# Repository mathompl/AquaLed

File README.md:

# AquaLed (en)

Arduino PWM LED lamp driver software with LCD support and temperature control for marine, reef or sweetwater aquariums.

Features:
- 8 channel PWM control of LED modules (drivers), with I2C module up to 512 (up to 8 channels on LCD)
- programmable light hours with sunsets and sunrises
- night light support
- 3 digital thermometers with asynchronous temperature read, for: water, lamp and addictional lamp or sump, controlling 3 separate  relays (cooling fans)
- customizable dimming, linear or logarithmic algorith
- bluetooth compatibility with AQma Led Control by Maqu http://magu.pl/aqma-led-control
- full configuration and status using Nextion 2.8" LCD with touch support, including: operational hours, sunset & sunrise hours, thermometers, dimming times, schedule, night mode etc.
- override programs: off, night and user accessible from LCD
- date/time support with RTC module
- screen saver with water temperature and time
- test mode
- moonphases simulation for night light
- all settings stored in EEPROM
- works on Arduino Nano

Example Nextion project attached. I dont have copyright for graphics used, use only as an example.

**Nextion LCD Screenshots**

**REQUIREMENTS:**

**Hardware:**
- Arduino Nano or better
- RTC module 
- Bluetooth (optional)
- 3x DS18B20 digital thermometers
- 3x 5v relays modules
- PCA9685 PWM i2c module (optional)
- Nextion 2.8" LCD

**Libraries:**
- Arduino-Temperature-Control-Library (https://github.com/milesburton/Arduino-Temperature-Control-Library) 
- DS1307RTC (https://github.com/PaulStoffregen/DS1307RTC)
- DS18B20 (https://github.com/nettigo/DS18B20)
- OneWire (https://github.com/PaulStoffregen/OneWire)
- Time (https://github.com/PaulStoffregen/Time)
- Adafruit-PWM-Servo-Driver-Library (https://github.com/adafruit/Adafruit-PWM-Servo-Driver-Library)
- or https://github.com/NachtRaveVL/PCA9685-Arduino

**Software:**
- Nextion Editor (https://nextion.itead.cc/download.html)
- Arduino IDE or atom.io

**Configuration:**
Driver configuration is in file aqualed.h

####PINS SETUP:
Configuration on LCD.

####Modules (uncomment to disable). As for now bluetooth and nextion support does not fit into Arduino Nano/UNO etc. flash memory. Use arduino Mega or disable one module support.
```
// modules, uncomment to disable, comment to enable
#define NO_BLUETOOTH
//#define NO_NEXTION
//#define NO_TEMPERATURE
```
####Other
There are many other options for eg. timers resolution, most of them are pretty self-explanatory ;)

**Wiring:**

# AquaLed (pl)

Sterownik lampy LED PWM na Arduino z obsługą termometrów, chłodzenia i wyświetlacza LCD Nextion dla akwariów słodko i słonowodnych.

Możliwości:
- obsługa 8 ściemnialnych kanałów PWM dla modułów LED (driverów), z modułem I2C do 512 kanałów (maksymalnie 8 na wyswietlaczu)
- programowanie godzin świetenia z symulacją wschodów i zachodów słońca
- światło nocne
- obsługa 3 cyfrowych termometrów sterujących pracą 3 przekaźników (np. wentylatorów), np. dla lampy, lampy w sumpie, wody w akwarium
- ściemnianie/rozjaśnianie
- kompatybilność z AQma Led Control by Maqu http://magu.pl/aqma-led-control w zakresie programowania przez Bluetooth
- pełna konfiguracja i status za pomocą wyświetlacza Nextion LCD (przykłady na 2,8"), sterowanie przez dotyk.
- możliwość chwilowego nadpisania działającego programu z wyświetlacza: wyłączenie/wymuszenie światła nocnego/program zdefiniowany
- obsługa godziny i daty
- wygaszacz ekranu z godziną i temperaturą wody
- tryb test
- symulacja faz księżyca
- wszystkie ustawienia zapamiętywane w pamięci EEPROM
- działa z Arduino Nano lub wyższym modelem

Przykładowy program na wyświetlacz załączony.

**Wygląd ekranów na wyświetlaczu **

**Wymagania:**

**Sprzęt:**
- Arduino Nano lub wyższy
- moduł czasu rzeczywistego RTC
- Bluetooth (opcjonalnie)
- 3x termometry cyfrowe DS18B20
- 3x moduły przekaźników 5v
- moduł PCA9685 PWM i2c  (optionalny)
- wyświetlacz Nextion 2.8" LCD lub większy

**Biblioteki:**
- Arduino-Temperature-Control-Library (https://github.com/milesburton/Arduino-Temperature-Control-Library)
- DS1307RTC (https://github.com/PaulStoffregen/DS1307RTC)
- DS18B20 (https://github.com/nettigo/DS18B20)
- OneWire (https://github.com/PaulStoffregen/OneWire)
- Time (https://github.com/PaulStoffregen/Time)
- Adafruit-PWM-Servo-Driver-Library (https://github.com/adafruit/Adafruit-PWM-Servo-Driver-Library)
- lub https://github.com/NachtRaveVL/PCA9685-Arduino

**Oprogramowanie:**
- Nextion Editor (https://nextion.itead.cc/download.html)
- Arduino IDE lub atom.io

**Konfiguracja:**
Konfiguracja w pliku aqualed.h i nextion.h

####Ustawienia pinów PWM:
Konfiguracja z poziomu wyświetlacza.

####Moduły (odkomentuj żeby wyłączyć). Uwaga! Obsługa bluetooth i nextio nie mieści się jednocześnie w pamięcy flash Arduino Nano/Uno itd. wchodzi tylko do Arduino Mega lub podobnego.
```
// modules, uncomment to disable, comment to enable
#define NO_BLUETOOTH
//#define NO_NEXTION
//#define NO_TEMPERATURE
```
####Inne
W pliku konfiguracyjnym można ustawić wiele opcji w tym czasy działania timerów, rozdzielczość załączania przekaźników itd. Większość ustawień wynika z samych nazw stałych :)

**Podłączenie:**

**PCB Prototype boards:**

Support:http://nano-reef.pl/topic/88904-a-qualed-sterownik-led-termometry-lcd-nextion/

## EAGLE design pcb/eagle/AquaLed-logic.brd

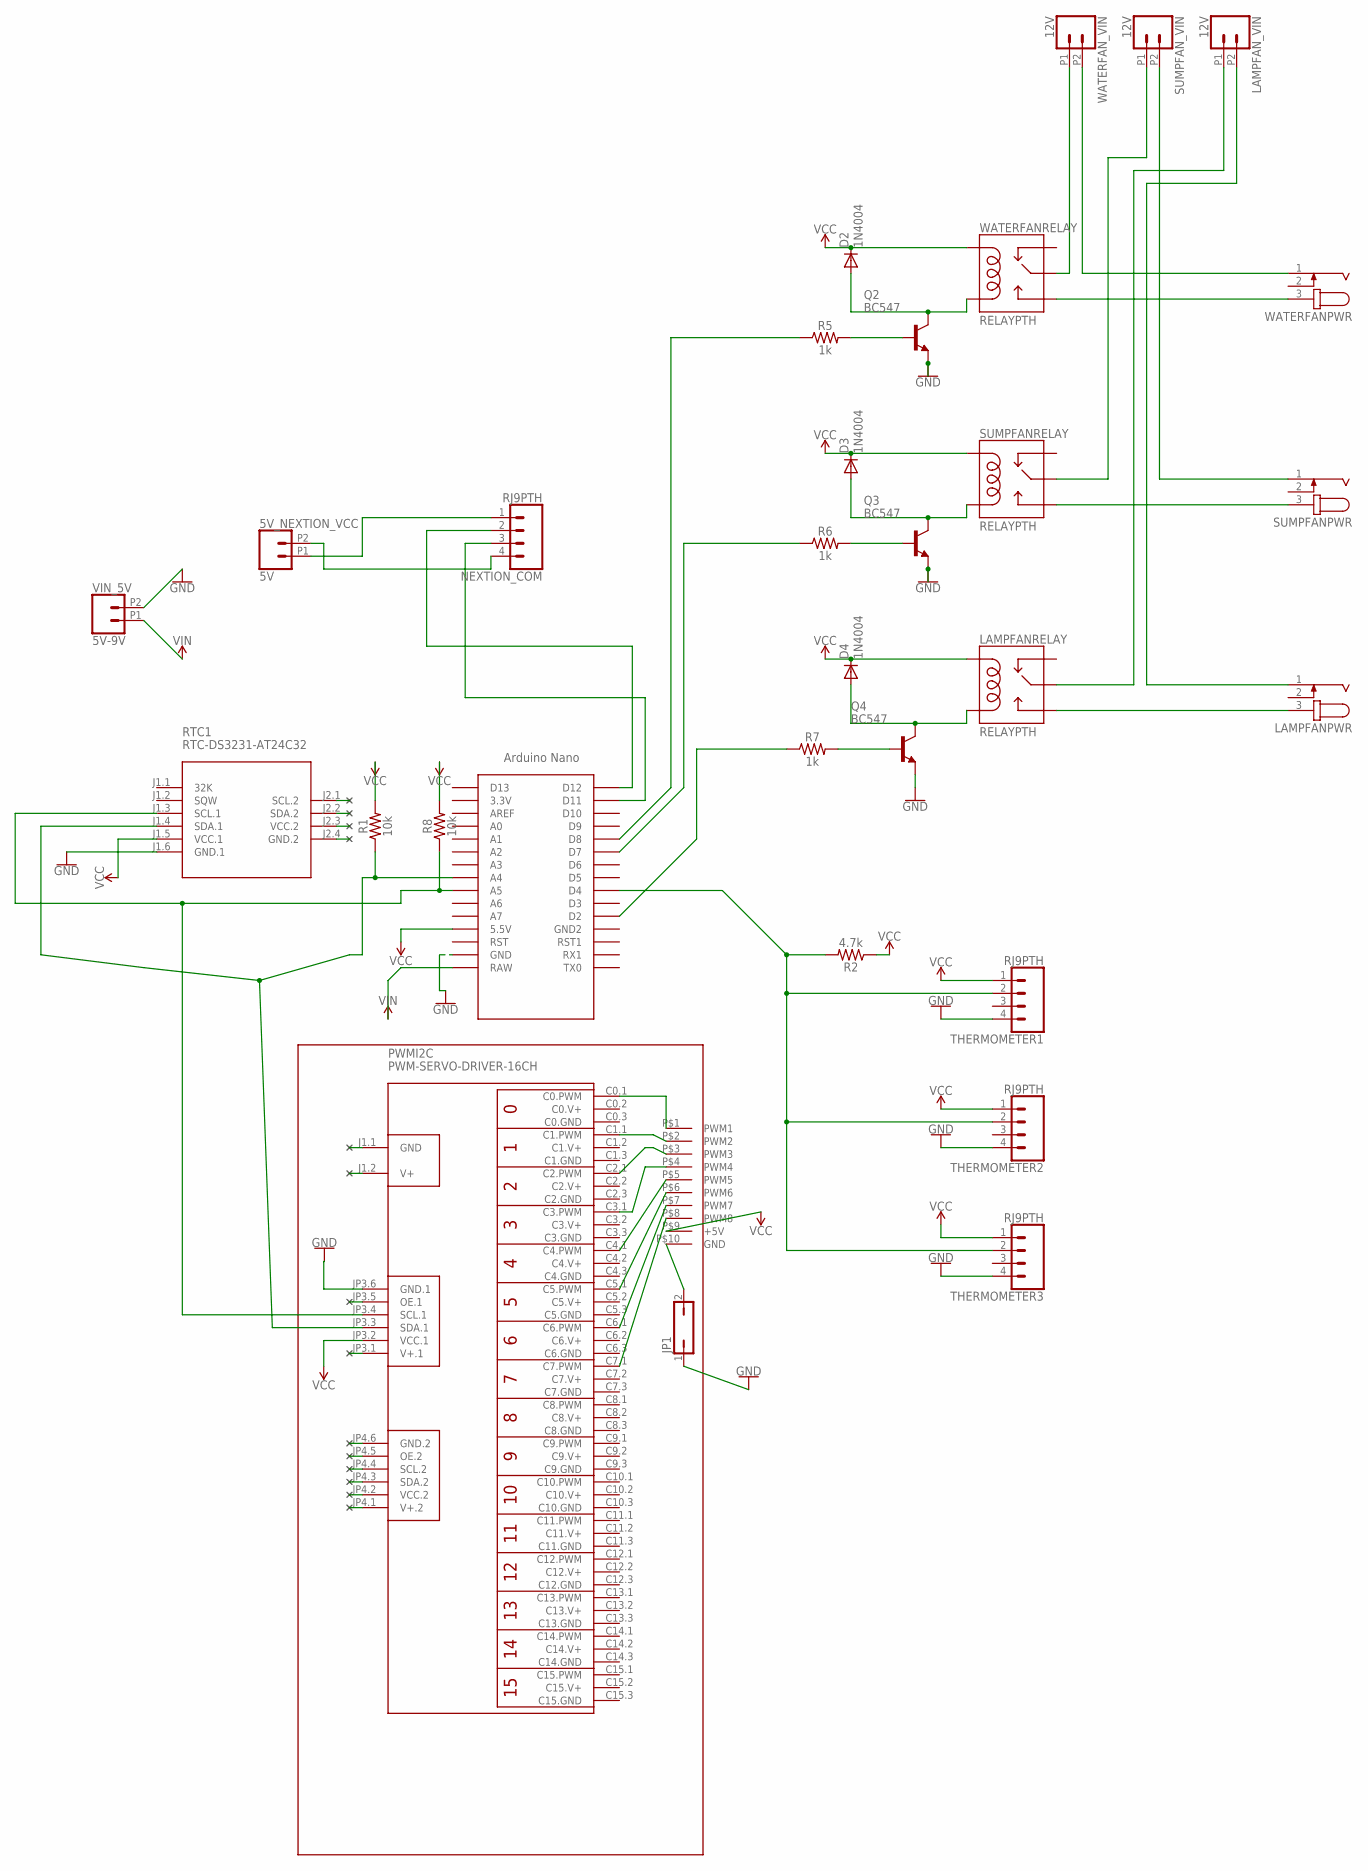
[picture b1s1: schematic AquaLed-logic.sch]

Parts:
5V_NEXTION_VCC: 5V; 1X02_2.54_SCREWTERM
D2, D3, D4: 1N4004; DO41-10
JP1: JP1Q; JP1
LAMPFANPWR: JACK-PLUG1; SPC4078
LAMPFANRELAY: RELAYPTH; SRD-05VDC-SL-C
LAMPFAN_VIN: 12V; 1X02_2.54_SCREWTERM
NEXTION_COM: RJ9PTH; RJ9
PWMI2C: PWM-SERVO-DRIVER-16CH
Q2, Q3, Q4: BC547; TO92
R1, R8: 10k; AXIAL-0.3
R2: 4.7k; AXIAL-0.3
R5, R6, R7: 1k; AXIAL-0.3
RTC1: RTC-DS3231-AT24C32
SUMPFANPWR: JACK-PLUG1; SPC4078
SUMPFANRELAY: RELAYPTH; SRD-05VDC-SL-C
SUMPFAN_VIN: 12V; 1X02_2.54_SCREWTERM
THERMOMETER1, THERMOMETER2, THERMOMETER3: RJ9PTH; RJ9
U$1: NANO
U$29: PCB
VIN_5V: 5V-9V; 1X02_2.54_SCREWTERM
WATERFANPWR: JACK-PLUG1; SPC4078
WATERFANRELAY: RELAYPTH; SRD-05VDC-SL-C
WATERFAN_VIN: 12V; 1X02_2.54_SCREWTERM

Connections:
GND: JP1.1, PWMI2C.JP3.6 (GND.1), Q2.1 (E), Q3.1 (E), Q4.1 (E), RTC1.J1.6 (GND.1), THERMOMETER1.4, THERMOMETER2.4, THERMOMETER3.4, U$1.GND, VIN_5V.P2 (2)
unnamed: R2.P$2 (2), THERMOMETER1.2, THERMOMETER2.2, THERMOMETER3.2, U$1.D4
unnamed: PWMI2C.JP3.3 (SDA.1), R1.P$1 (1), RTC1.J1.4 (SDA.1), U$1.A4
unnamed: R5.P$1 (1), U$1.D8
unnamed: R6.P$1 (1), U$1.D7
unnamed: LAMPFANPWR.3, LAMPFANRELAY.SWOPEN
unnamed: SUMPFANPWR.3, SUMPFANRELAY.SWOPEN
unnamed: LAMPFANRELAY.SWCOMMON, LAMPFAN_VIN.P1 (1)
unnamed: R7.P$1 (1), U$1.D2
unnamed: D2.A, Q2.3 (C), WATERFANRELAY.COIL0
unnamed: Q2.2 (B), R5.P$2 (2)
unnamed: SUMPFANPWR.1, SUMPFAN_VIN.P2 (2)
unnamed: D3.A, Q3.3 (C), SUMPFANRELAY.COIL0
unnamed: Q3.2 (B), R6.P$2 (2)
unnamed: LAMPFANPWR.1, LAMPFAN_VIN.P2 (2)
unnamed: D4.A, LAMPFANRELAY.COIL0, Q4.3 (C)
unnamed: Q4.2 (B), R7.P$2 (2)
unnamed: SUMPFANRELAY.SWCOMMON, SUMPFAN_VIN.P1 (1)
unnamed: WATERFANRELAY.SWCOMMON, WATERFAN_VIN.P1 (1)
unnamed: WATERFANPWR.1, WATERFAN_VIN.P2 (2)
unnamed: WATERFANPWR.3, WATERFANRELAY.SWOPEN
unnamed: 5V_NEXTION_VCC.P1 (1), NEXTION_COM.1
unnamed: 5V_NEXTION_VCC.P2 (2), NEXTION_COM.4
unnamed: NEXTION_COM.3, U$1.D11
unnamed: NEXTION_COM.2, U$1.D12
unnamed: PWMI2C.JP3.4 (SCL.1), R8.P$1 (1), RTC1.J1.3 (SCL.1), U$1.A5
unnamed: PWMI2C.C0.1 (C0.PWM), U$29.P$1 (PWM1)
unnamed: PWMI2C.C1.1 (C1.PWM), U$29.P$2 (PWM2)
unnamed: PWMI2C.C2.1 (C2.PWM), U$29.P$3 (PWM3)
unnamed: PWMI2C.C3.1 (C3.PWM), U$29.P$4 (PWM4)
unnamed: PWMI2C.C4.1 (C4.PWM), U$29.P$5 (PWM5)
unnamed: PWMI2C.C5.1 (C5.PWM), U$29.P$6 (PWM6)
unnamed: PWMI2C.C6.1 (C6.PWM), U$29.P$7 (PWM7)
unnamed: PWMI2C.C7.1 (C7.PWM), U$29.P$8 (PWM8)
unnamed: JP1.2, U$29.P$10 (GND)
VCC: D2.C, D3.C, D4.C, LAMPFANRELAY.COIL1, PWMI2C.JP3.2 (VCC.1), R1.P$2 (2), R2.P$1 (1), R8.P$2 (2), RTC1.J1.5 (VCC.1), SUMPFANRELAY.COIL1, THERMOMETER1.1, THERMOMETER2.1, THERMOMETER3.1, U$1.5V (5.5V), U$29.P$9 (+5V), WATERFANRELAY.COIL1
VIN: U$1.RAW, VIN_5V.P1 (1)

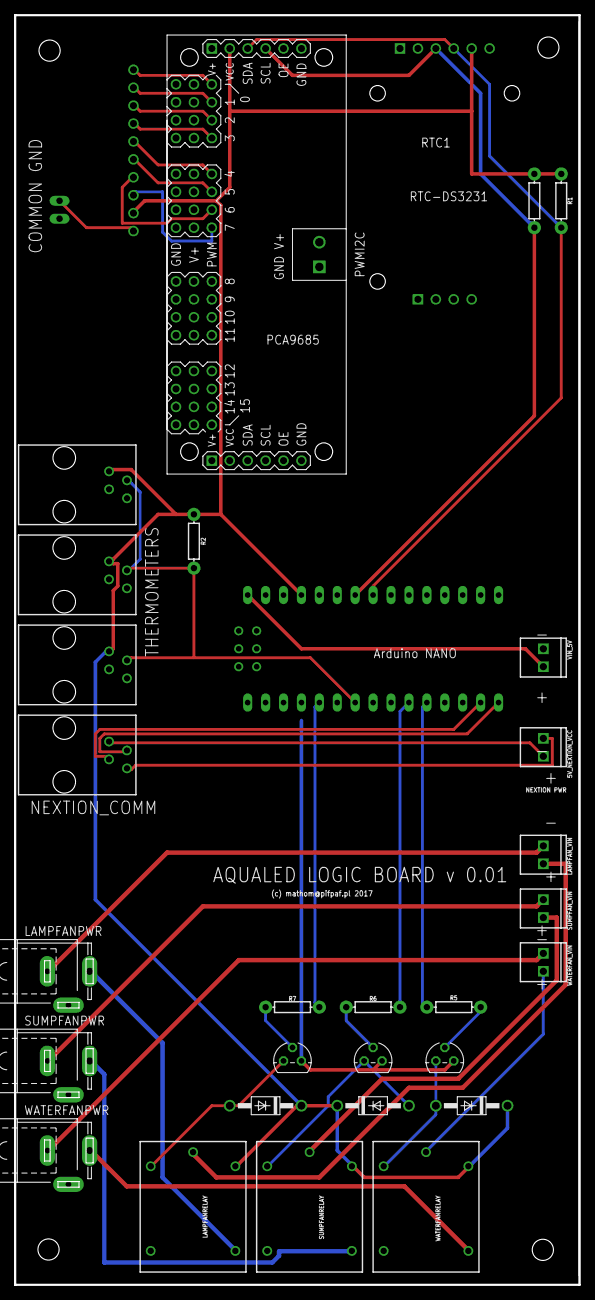
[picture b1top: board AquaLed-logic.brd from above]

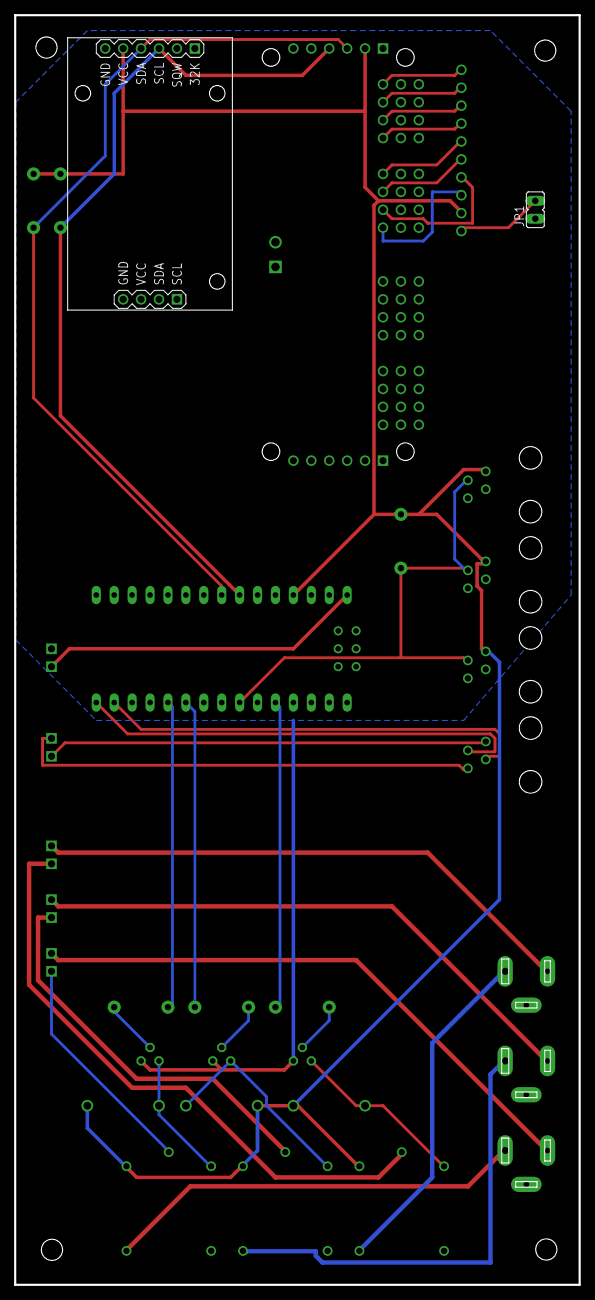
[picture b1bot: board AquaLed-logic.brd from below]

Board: 2 copper layers, 80.0 x 180.0 mm, 32 parts (2 on the bottom side), 37 nets.

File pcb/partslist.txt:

Partlist

Exported from AquaLEd-drivers.sch at 2017-11-26 09:05

EAGLE Version 8.4.1 Copyright (c) 1988-2017 Autodesk, Inc.

Assembly variant:

Part     Value          Device     Package  Library          Sheet

DRIVER1                 LDD-H      LDD-H    meanwell_dcdc_v8 1
DRIVER2                 LDD-H      LDD-H    meanwell_dcdc_v8 1
DRIVER3                 LDD-H      LDD-H    meanwell_dcdc_v8 1
DRIVER4                 LDD-H      LDD-H    meanwell_dcdc_v8 1
DRIVER5                 LDD-H      LDD-H    meanwell_dcdc_v8 1
DRIVER6                 LDD-H      LDD-H    meanwell_dcdc_v8 1
DRIVER7                 LDD-H      LDD-H    meanwell_dcdc_v8 1
DRIVER8                 LDD-H      LDD-H    meanwell_dcdc_v8 1
POWERIN                 W237-102   W237-102 con-wago-500     1
PWM1                    JACK-PLUG1 SPC4078  con-jack         1
PWM2                    JACK-PLUG1 SPC4078  con-jack         1
PWM3                    JACK-PLUG1 SPC4078  con-jack         1
PWM4                    JACK-PLUG1 SPC4078  con-jack         1
PWM5                    JACK-PLUG1 SPC4078  con-jack         1
PWM6                    JACK-PLUG1 SPC4078  con-jack         1
PWM7                    JACK-PLUG1 SPC4078  con-jack         1
PWM8                    JACK-PLUG1 SPC4078  con-jack         1

Partlist

Exported from AquaLed-logic.sch at 2017-11-26 09:06

EAGLE Version 8.4.1 Copyright (c) 1988-2017 Autodesk, Inc.

Assembly variant:

Part           Value                 Device                  Package               Library             Sheet

5V_NEXTION_VCC 5V                    CONN_022.54MM_SCREWTERM 1X02_2.54_SCREWTERM   SparkFun-Connectors 1
D2             1N4004                1N4004                  DO41-10               diode               1
D3             1N4004                1N4004                  DO41-10               diode               1
D4             1N4004                1N4004                  DO41-10               diode               1
JP1                                  JP1Q                    JP1                   jumper              1
LAMPFANPWR                           JACK-PLUG1              SPC4078               con-jack            1
LAMPFANRELAY   RELAYPTH              RELAYPTH                SRD-05VDC-SL-C        SRD-05VDC-SL-C      1
LAMPFAN_VIN    12V                   CONN_022.54MM_SCREWTERM 1X02_2.54_SCREWTERM   SparkFun-Connectors 1
NEXTION_COM    RJ9PTH                RJ9PTH                  RJ9                   SparkFun-Retired    1
PWMI2C         PWM-SERVO-DRIVER-16CH PWM-SERVO-DRIVER-16CH   PWM-SERVO-DRIVER-16CH diy-modules         1
Q2             BC547                 BC547                   TO92                  transistor-npn      1
Q3             BC547                 BC547                   TO92                  transistor-npn      1
Q4             BC547                 BC547                   TO92                  transistor-npn      1
R1             10k                   10KOHM-HORIZ-1/6W-5%    AXIAL-0.3             SparkFun-Resistors  1
R2             4.7k                  RESISTORAXIAL-0.3       AXIAL-0.3             SparkFun-Resistors  1
R5             1k                    10KOHM-HORIZ-1/4W-1%    AXIAL-0.3             SparkFun-Resistors  1
R6             1k                    10KOHM-HORIZ-1/4W-1%    AXIAL-0.3             SparkFun-Resistors  1
R7             1k                    10KOHM-HORIZ-1/4W-1%    AXIAL-0.3             SparkFun-Resistors  1
R8             10k                   10KOHM-HORIZ-1/6W-5%    AXIAL-0.3             SparkFun-Resistors  1
RTC1           RTC-DS3231-AT24C32    RTC-DS3231-AT24C32      RTC-DS3231-AT24C32    diy-modules         1
SUMPFANPWR                           JACK-PLUG1              SPC4078               con-jack            1
SUMPFANRELAY   RELAYPTH              RELAYPTH                SRD-05VDC-SL-C        SRD-05VDC-SL-C      1
SUMPFAN_VIN    12V                   CONN_022.54MM_SCREWTERM 1X02_2.54_SCREWTERM   SparkFun-Connectors 1
THERMOMETER1   RJ9PTH                RJ9PTH                  RJ9                   SparkFun-Retired    1
THERMOMETER2   RJ9PTH                RJ9PTH                  RJ9                   SparkFun-Retired    1
THERMOMETER3   RJ9PTH                RJ9PTH                  RJ9                   SparkFun-Retired    1
U$1            NANO                  NANO                    NANO                  Arduino-clone       1
U$29           PCB                   PCB                     PCB                   aqualed             1
VIN_5V         5V-9V                 CONN_022.54MM_SCREWTERM 1X02_2.54_SCREWTERM   SparkFun-Connectors 1
WATERFANPWR                          JACK-PLUG1              SPC4078               con-jack            1
WATERFANRELAY  RELAYPTH              RELAYPTH                SRD-05VDC-SL-C        SRD-05VDC-SL-C      1
WATERFAN_VIN   12V                   CONN_022.54MM_SCREWTERM 1X02_2.54_SCREWTERM   SparkFun-Connectors 1

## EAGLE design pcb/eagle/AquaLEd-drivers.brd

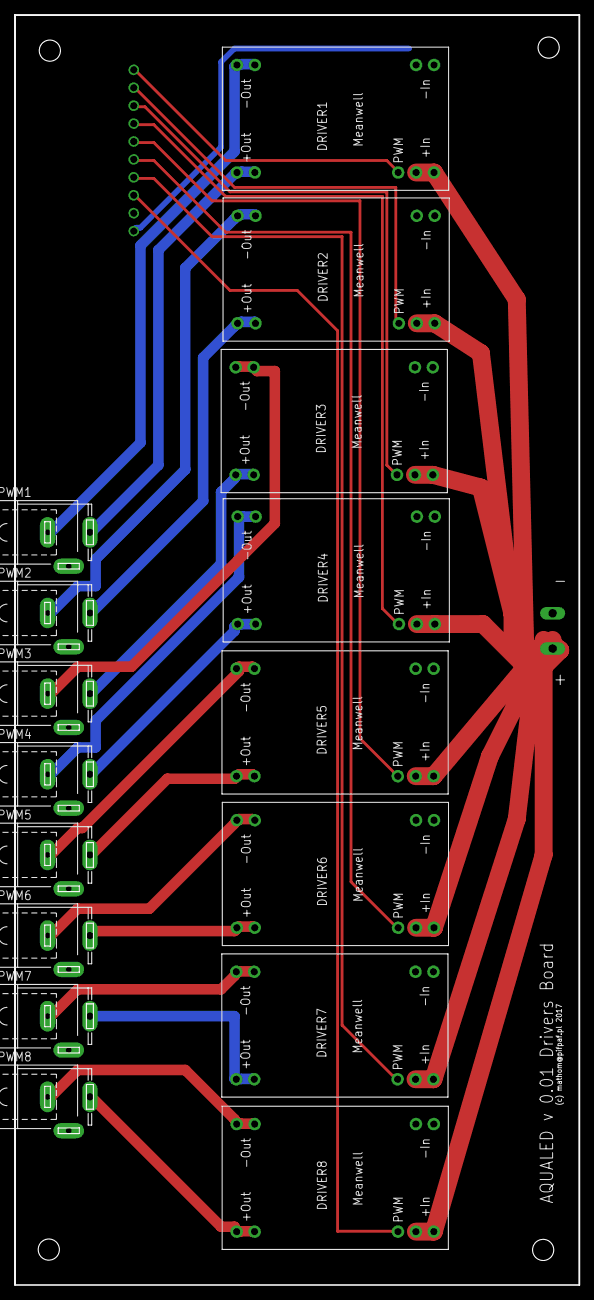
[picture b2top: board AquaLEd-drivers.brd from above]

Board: 2 copper layers, 80.0 x 180.0 mm, 18 parts (1 on the bottom side), 26 nets.

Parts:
DRIVER1, DRIVER2, DRIVER3, DRIVER4, DRIVER5, DRIVER6, DRIVER7, DRIVER8: LDD-H
POWERIN: W237-102
PWM1, PWM2, PWM3, PWM4, PWM5, PWM6, PWM7, PWM8: SPC4078
U$29: PCB

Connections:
GND: DRIVER1.1, DRIVER1.2, DRIVER2.1, DRIVER2.2, DRIVER3.1, DRIVER3.2, DRIVER4.1, DRIVER4.2, DRIVER5.1, DRIVER5.2, DRIVER6.1, DRIVER6.2, DRIVER7.1, DRIVER7.2, DRIVER8.1, DRIVER8.2, POWERIN.1, U$29.P$10
unnamed: DRIVER1.22, U$29.P$1
unnamed: DRIVER8.11, DRIVER8.12, PWM8.1
unnamed: DRIVER8.13, DRIVER8.14, PWM8.3
unnamed: DRIVER7.11, DRIVER7.12, PWM7.1
unnamed: DRIVER7.13, DRIVER7.14, PWM7.3
unnamed: DRIVER6.11, DRIVER6.12, PWM6.1
unnamed: DRIVER6.13, DRIVER6.14, PWM6.3
unnamed: DRIVER5.11, DRIVER5.12, PWM5.1
unnamed: DRIVER5.13, DRIVER5.14, PWM5.3
unnamed: DRIVER4.11, DRIVER4.12, PWM4.1
unnamed: DRIVER4.13, DRIVER4.14, PWM4.3
unnamed: DRIVER3.11, DRIVER3.12, PWM3.1
unnamed: DRIVER3.13, DRIVER3.14, PWM3.3
unnamed: DRIVER2.11, DRIVER2.12, PWM2.1
unnamed: DRIVER2.13, DRIVER2.14, PWM2.3
unnamed: DRIVER1.11, DRIVER1.12, PWM1.1
unnamed: DRIVER1.13, DRIVER1.14, PWM1.3
unnamed: DRIVER2.22, U$29.P$2
unnamed: DRIVER3.22, U$29.P$3
unnamed: DRIVER4.22, U$29.P$4
unnamed: DRIVER5.22, U$29.P$5
unnamed: DRIVER6.22, U$29.P$6
unnamed: DRIVER7.22, U$29.P$7
unnamed: DRIVER8.22, U$29.P$8
VIN: DRIVER1.23, DRIVER1.24, DRIVER2.23, DRIVER2.24, DRIVER3.23, DRIVER3.24, DRIVER4.23, DRIVER4.24, DRIVER5.23, DRIVER5.24, DRIVER6.23, DRIVER6.24, DRIVER7.23, DRIVER7.24, DRIVER8.23, DRIVER8.24, POWERIN.2

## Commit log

2016-10-26 First import
2016-10-26 Nextion example
2016-10-26 nx demo
2016-10-26 tidy up
2016-10-27 nextion demo english version
2016-10-27 code tidy up
2016-10-27 comments
2016-10-27 bugfixes
2016-10-28 wiring diagram
2016-10-29 dark bg
2016-10-30 fixed serious bug in sunsets (wrong data types)
2016-10-30 performance tweaks
2016-11-01 Warning: Nextion Editor has a BUG. Files saved on computers with different DPI settings are messed up when opened on PC with other DPI settings. nextion-demo.hmi is for 96dpi now, and there is also f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
2016-11-02 i2c settings (pwm i2c module)
2016-11-03 i2c frequency in cofig
2016-11-08 fixed bug in setting Nextion baud rate
2016-11-13 define no_temperature not everywhere
2016-11-14 moved dimmingTable from sram to flash
2016-11-14 added settings of lcd backlit level
2016-11-15 small bugfixes
2016-11-15 memory free lib in debug mode only
2016-12-23 Build-in/i2c PWM default values switching configured by USE_I2C_PWM_MODULE compiler directive
2017-01-01 fixed serious bug preventing dimming time to be >30s (variable overflow)
2017-01-26 added: schedule menu current time startx and starty
2017-01-31 bugfix
2017-01-31 fixed serious bug with sunset & sunrise lenght
2017-02-03 Fixed numerous bugs: - when sunset ended before scheduled hour, nightmode was not kicking in - increased sunset/sunrise resolution, in certain situations sunset/sunrise time was shorter then schedule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
    New features:
    - after crash or forced mode lamp recovers to last state (usefull for sunset/sunrises) - needs testing
    - added switch for forcing nightlight value - #define PWM_FORCE_NIGHT_VALUE 1 -when 1% is too much
    - added constant #define WATER_TEMPERATURE_MIN for defining minimal water temperature used for coloring temperature on screensaver page
2017-02-03 default builtin pwms
2017-02-04 fixed minor bug
2017-02-05 fixed bug when sunset was not starting
2017-02-05 added i2c_invert variable for i2c modules with inverted scale
2017-02-06 fixed bug when pwmSaved was not updated during normal operation
2017-02-06 sunset && sunrise times were off again ;) fixed
2017-02-07 bugfixes, new icons on Nextion screen
2017-02-07 rollback, nextion fonts can be only in 1:2 aspect ratio.icons look bad :(
2017-02-08 icons
2017-02-09 fixed buttons on settings page
2017-02-11 documentation
2017-03-01 added Nextion 4.3" file and pcb layout made by sq6kbr (nano-reef.pl forum)
2017-03-08 - rewritten nextion functions - cleaner and more friendly code - channel names set from software - restore sunset/sunrise after crash or manual mode - disable/enable user mode (with star) - all harwa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
2017-03-08 hotfix
2017-03-27 fixed dst time
2017-05-20 fixed 4.3 nextion file
2017-05-27 fixed sunset/sunrise bug
2017-05-28 fixed dst time fixed bug caused forced mode during sunset/sunrise to hang
2017-05-28 fixed bug when dimming to nightlight during sunset turned off the lamp for one cycle
2017-11-26 added PCB prototype board Eagle Cad and Gerber files
2017-11-26 added schematics images
2017-12-03 change recovery
2017-12-05 added moonphase simulation, fixed many bugs, reduced code, sunset/sunrise value recovery after shutdown/forced user mode
2017-12-07 WARNING! EEPROM structure changed! DAY & PROG Values need to be re-set.
    - further code optimization (saved approx. 2kb)
    - code tidy-up for pwm data : settings and runtime data separated
    - added new screens: for saving data and critical error (lamp overheating
    and max wattage exceeding - set max values in config.h as needed)
    - pwm values now stored as: int (range 0-4048) for user prog and day
    values and raw data for nigh value (0-255). Night values dont map to pwm
2017-12-08 bugfix.
2017-12-11 optimizations
2017-12-11 optimization
2017-12-17 temperature bugfix
2017-12-22 changed i2c library to https://github.com/NachtRaveVL/PCA9685-Arduino You can still use old Adafruit library, just uncomment //#define USE_ADAFRUIT_LIBRARY in config.h
2017-12-22 Create LICENSE
2018-01-15 - Performance tweaks, bug fixes. - channel status - manualy switch relay on/off
2018-01-15 updated nextion files
2018-01-20 sunrise/sunset didn't stop in time
2018-02-28 baud bugfix
2018-02-28 nextion settime bugfix
2018-03-01 bugfixes of bugfixes :)
2018-03-04 small changes
2019-10-17 fresh
2019-10-17 Fixed nextion files
2019-10-17 Fixed and cleaned platformio dependencies. Removed non-120dpi nextion files - need to be reworked.
2019-10-22 fixed blootooth module
2021-06-14 new PCA9685 fix
2022-05-07 critical and performance fixes
    1. in nxTouch() there wasn't check on array lenght in read.serial()
    2. in pwm() there was not necessary calls to RTC.now() in each
    iteration. Reading RTC time now moved to separate funcion called every
    1s
    3. added Wire.setWireTimeout() for i2c devices
    4. other fixes and tweaks
2022-05-07 moved to src
2022-05-07 move to src
2022-05-07 fixed first time read
2022-05-09 added eeprom settings defaults
2022-05-14 stable
2022-05-14 Commit development version.
    moved all methods to classes
2022-05-14 Delete devs directory
    delete trash
2022-05-14 Delete Nextion/compiled directory
    delete
2022-05-14 datastore changes
2022-05-14 EEPROM - removed AQMA compatibility (for future upgrade to arduino 33 with wifi support)
2022-05-15 several fixes

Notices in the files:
parts and their libraries:
SparkFun-Connectors: Licensing: Creative Commons ShareAlike 4.0 International - https://creativecommons.org/licenses/by-sa/4.0
diy-modules: Released under the Creative Commons Attribution 4.0 International License: http://creativecommons.org/licenses/by/4.0
